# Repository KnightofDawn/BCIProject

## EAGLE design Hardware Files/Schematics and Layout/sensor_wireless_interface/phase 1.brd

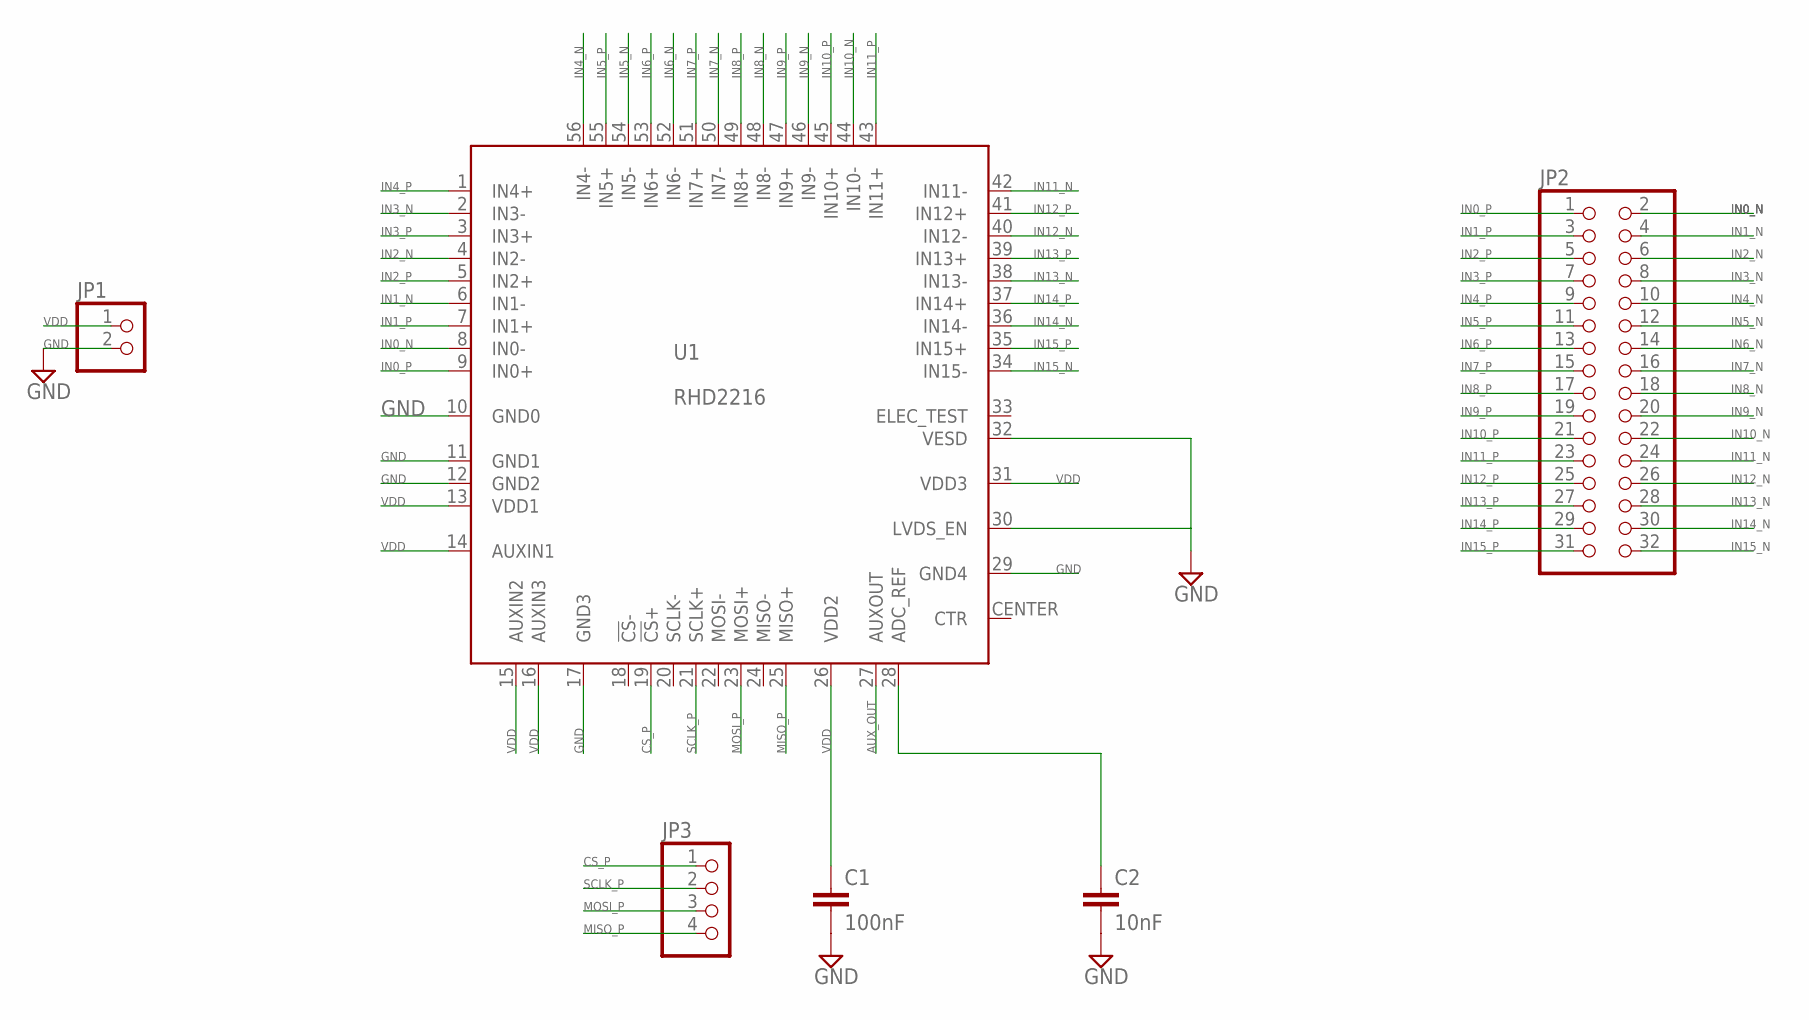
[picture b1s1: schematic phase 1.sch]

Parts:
C1: 100nF; C2.5-2
C2: 10nF; C2.5-2
JP1: PINHD-1X2; 1X02
JP2: PINHD-2X16; 2X16
JP3: PINHD-1X4; 1X04
U1: RHD2216; ZIF_QFN56_8_X_8_MLF00056A1

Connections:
AUX_OUT: U1.27 (AUXOUT)
CS_P: JP3.1, U1.19 (!CS!+)
CTR: U1.CENTER (CTR)
GND: C1.2, C2.2, JP1.2, U1.10 (GND0), U1.11 (GND1), U1.12 (GND2), U1.17 (GND3), U1.29 (GND4), U1.30 (LVDS_EN), U1.32 (VESD)
IN0_N: JP2.2, U1.8 (IN0-)
IN0_P: JP2.1, U1.9 (IN0+)
IN1_N: JP2.4, U1.6 (IN1-)
IN1_P: JP2.3, U1.7 (IN1+)
IN2_N: JP2.6, U1.4 (IN2-)
IN2_P: JP2.5, U1.5 (IN2+)
IN3_N: JP2.8, U1.2 (IN3-)
IN3_P: JP2.7, U1.3 (IN3+)
IN4_N: JP2.10, U1.56 (IN4-)
IN4_P: JP2.9, U1.1 (IN4+)
IN5_N: JP2.12, U1.54 (IN5-)
IN5_P: JP2.11, U1.55 (IN5+)
IN6_N: JP2.14, U1.52 (IN6-)
IN6_P: JP2.13, U1.53 (IN6+)
IN7_N: JP2.16, U1.50 (IN7-)
IN7_P: JP2.15, U1.51 (IN7+)
IN8_N: JP2.18, U1.48 (IN8-)
IN8_P: JP2.17, U1.49 (IN8+)
IN9_N: JP2.20, U1.46 (IN9-)
IN9_P: JP2.19, U1.47 (IN9+)
IN10_N: JP2.22, U1.44 (IN10-)
IN10_P: JP2.21, U1.45 (IN10+)
IN11_N: JP2.24, U1.42 (IN11-)
IN11_P: JP2.23, U1.43 (IN11+)
IN12_N: JP2.26, U1.40 (IN12-)
IN12_P: JP2.25, U1.41 (IN12+)
IN13_N: JP2.28, U1.38 (IN13-)
IN13_P: JP2.27, U1.39 (IN13+)
IN14_N: JP2.30, U1.36 (IN14-)
IN14_P: JP2.29, U1.37 (IN14+)
IN15_N: JP2.32, U1.34 (IN15-)
IN15_P: JP2.31, U1.35 (IN15+)
MISO_P: JP3.4, U1.25 (MISO+)
MOSI_P: JP3.3, U1.23 (MOSI+)
unnamed: C2.1, U1.28 (ADC_REF)
SCLK_P: JP3.2, U1.21 (SCLK+)
VDD: C1.1, JP1.1, U1.13 (VDD1), U1.14 (AUXIN1), U1.15 (AUXIN2), U1.16 (AUXIN3), U1.26 (VDD2), U1.31 (VDD3)

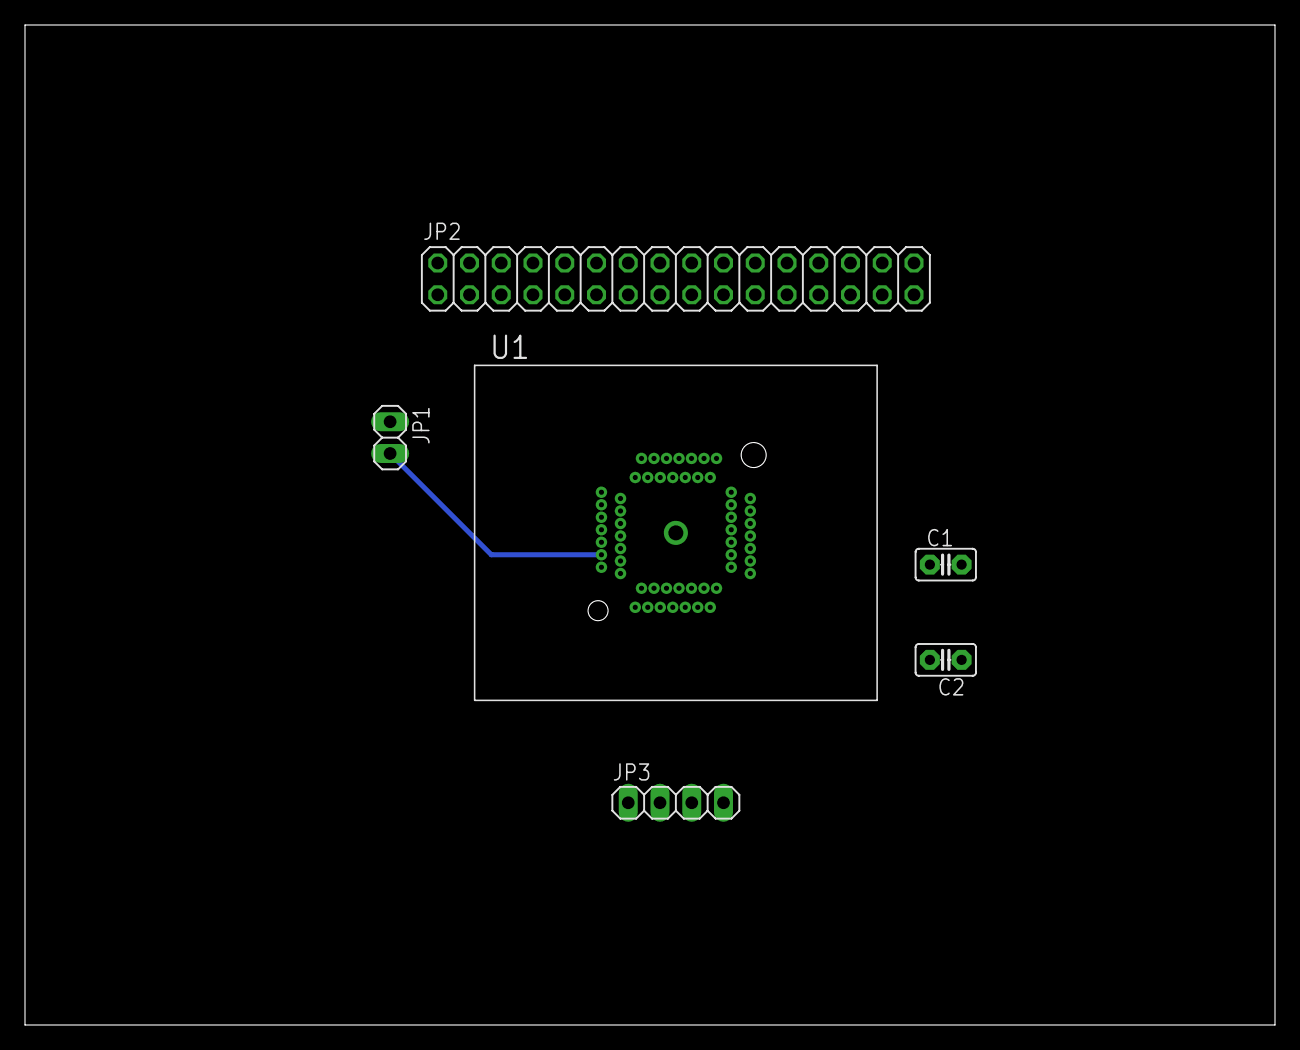
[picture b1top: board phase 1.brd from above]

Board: 2 copper layers, 100.0 x 80.0 mm, 6 parts (0 on the bottom side), 39 nets.

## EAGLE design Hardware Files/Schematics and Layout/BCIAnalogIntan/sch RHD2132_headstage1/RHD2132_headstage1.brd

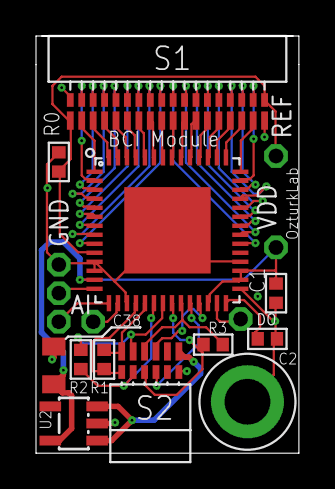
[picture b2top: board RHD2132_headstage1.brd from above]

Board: 4 copper layers, 14.6 x 23.2 mm, 19 parts (0 on the bottom side), 49 nets.

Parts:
AI: TESTPOINT_SMALL
C1: 100n; 0402
C2: 10n; 0402
C38: 10uF; R/2012-12R
DO: TESTPOINT_SMALL
GND: TESTPOINT_SMALL
H1: SCREW_HOLE_2-56
IN2, IN3: TESTPOINT_SMALL
R0: 0; 0402
R1, R2, R3: 100; 0402
REF: TESTPOINT_SMALL
S1: OMNETICS_A79025
S2: RHD2000-CABLE-AMP-SIDE; OMNETICS_PZN-12-AA
U1: RHD2132_QFN; QFN56_8_X_8_LARGE
U2: FAN2500S33X; SOT23-5$2
VDD: TESTPOINT_SMALL

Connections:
5V: S2.T6, U2.1, U2.3
GND: C1.2, C2.2, C38.-, GND.1, H1.1, R0.1, S1.B1, S1.T18, S2.B6, U1.11, U1.12, U1.17, U1.29, U1.32, U1.CENTER, U2.2
unnamed: R0.2, REF.1, S1.B18, S1.T1, U1.10
unnamed: S1.B3, U1.3
unnamed: S1.B2, U1.2
unnamed: S1.B4, U1.4
unnamed: S1.B5, U1.5
unnamed: S1.B6, U1.6
unnamed: S1.B7, U1.7
unnamed: S1.B8, U1.8
unnamed: S1.B9, U1.9
unnamed: R1.1, S2.B1, U1.18
unnamed: S1.B17, U1.41
unnamed: S1.B16, U1.40
unnamed: S1.B15, U1.39
unnamed: S1.B14, U1.38
unnamed: S1.B13, U1.37
unnamed: S1.B12, U1.36
unnamed: S1.B11, U1.35
unnamed: S1.T9, U1.50
unnamed: S1.T8, U1.51
unnamed: S1.T7, U1.52
unnamed: S1.T3, U1.56
unnamed: S1.T4, U1.55
unnamed: S1.T5, U1.54
unnamed: S1.T6, U1.53
unnamed: S1.T10, U1.49
unnamed: S1.T11, U1.48
unnamed: S1.T12, U1.47
unnamed: S1.T13, U1.46
unnamed: S1.T14, U1.45
unnamed: S1.T15, U1.44
unnamed: S1.T16, U1.43
unnamed: S1.T2, U1.1
unnamed: S1.T17, U1.42
unnamed: R1.2, S2.T1, U1.19
unnamed: R2.1, S2.B2, U1.20
unnamed: R2.2, S2.T2, U1.21
unnamed: R3.1, S2.B3, U1.22
unnamed: R3.2, S2.T3, U1.23
unnamed: S2.B4, U1.24
unnamed: S2.T4, U1.25
unnamed: C2.1, U1.28
unnamed: DO.1, U1.27
unnamed: AI.1, U1.14
unnamed: IN2.1, U1.15
unnamed: IN3.1, U1.16
unnamed: S1.B10, U1.34
VCC: C1.1, C38.+, U1.13, U1.26, U1.30, U1.31, U2.5, VDD.1

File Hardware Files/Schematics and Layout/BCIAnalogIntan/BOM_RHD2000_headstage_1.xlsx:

Bill of Materials |  | RHD2000 Headstage Board 1
Part | Value | Device | Package | Digi-Key part number | Notes
C1 | 100 nF (0.1 uF) | ceramic capacitor (25 V) | 0402 | 445-4964-1-ND
C2 | 10 nF (10000 pF) | ceramic capacitor (25 V) | 0402 | 490-1312-1-ND
R0 | 0 | resistor | 0402 | P0.0JCT-ND
R1 | 100 | resistor | 0402 | P100JCT-ND
R2 | 100 | resistor | 0402 | P100JCT-ND
R3 | 100 | resistor | 0402 | P100JCT-ND
S1 | NSD-36-AA-GS | nano strip connector | 36-pin, 4 guides | Omnetics A79025-001
S2 | PZN-12-AA | polarized nano connector | polarized 12-pin | Omnetics A79623-001
U1 | RHD2132 or RHD2216 | 32-channel amplifier chip | QFN-56L | Intan RHD2132/RHD2216
U2 | FAN2500S33X | V_REG_LDOSMD | SOT23-5$2 | IC REG LDO 3.3V .1A SOT-23-5 | FAN2500S33X | FAN2500S33XCT-ND

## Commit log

2013-02-27 new ref added
2013-02-27 New reference publications added
2013-02-27 nrf development tools added
2013-02-28 not needed
2013-02-28 initial check-in
2013-03-02 schematic and layout for ZIF breakout
2013-03-06 updated pin assignment for better routing
2013-03-06 initial check in
2013-03-20 changed to more specific schematic
2013-03-20 added another pin header for AUXIN*
2013-03-27 connect AUXIN1-2-3 to VDD to save power
2013-03-29 initial check source code and library
2013-04-02 nothing new
2013-04-10 hardware design added
2013-04-12 BOM added to RHG project
2013-04-12 breakout boardss are added
2013-04-12 Intan socket board added
2013-04-12 update 36 pin breakout
2013-04-12 Update 12 Pin Breakout
2013-04-12 Update Intan Socket Board
2013-04-15 updated intan socket board
2013-04-15 BrainApp Directory Added
2013-04-16 pbrain software added
2013-04-16 pbrain added
2013-04-17 added bci centroid file for board assembly for screaming circuits
2013-04-17 Neuroregab slides added
2013-04-17 source added
2013-04-18 updated slides
2013-04-18 BCI Work Plan updated
2013-04-18 Nordic IOS6 Application Source Code
2013-04-18 added BOM file for Screaming Circuits for the BCI Module
2013-04-18 third party software added
2013-04-19 updated intan hardware files
2013-04-20 updated source code
2013-04-22 removed .gpi information files from the 36pin breakout board gerber files
2013-04-22 removed .gpi information file from 12 pin breakout gerber files
2013-04-24 updated source code v0.1
2013-04-24 intan now a 4 layer board
2013-04-24 updated source code v0.2
2013-04-24 change rs232 and spi to port 0
2013-04-24 reorganize
2013-04-25 Rehabilitation matter for an new project proposal
2013-04-25 update hardware files
2013-04-25 updated source code 0424
2013-04-25 added pad layer folder with gerber for RHD2132
2013-04-25 pad files added
2013-04-28 updated source code 0426
2013-04-29 updated source code 0428
2013-04-30 updated source code 0429 and firmware code
2013-04-30 review files added
2013-04-30 New presentyations added
2013-04-30 slides added
2013-05-01 updated source code 0430 with data in lists
2013-05-01 Yi Su's code modified for plots and threads
2013-05-02 Update for Rehabilitation and Brain Imaging
2013-05-02 updated code 0501
2013-05-03 updated source code 0502
2013-05-06 Blue Tooth Dongle Application
    BLE Dongle Application for PC to receive the data from bluetooth dongle
    and get it send to web with web service with local database of
    refreshing.
    Two major application was zipped, one is for blue tooth recognized with
    Serial port to send data to web. The other one is for PC as web service
    server with local database for refreshing in web browser.
2013-05-07 updated source code 0506
2013-05-07 updated source code 0506_v2
2013-06-29 0628_v1_Intan board added

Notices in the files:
parts and their libraries:
SparkFun: Licensing: CC v3.0 Share-Alike You are welcome to use this library for commercial purposes.
